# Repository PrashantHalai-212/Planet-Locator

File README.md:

# Planet Locator – GPS Planet Finder

Battery-powered board that shows which planets are in your sky right now. It gets time and position from GPS, calculates where the Moon and planets are directly on an ESP32-C3, and lights an LED for every planet higher than 25° above the horizon. Designed in KiCad 10, 2-layer round PCB made by AISLER, hand-assembled. Group project with Bineth for Practical Electronics (WS 2026) at Rhine-Waal University.

## Specs

| | |
|---|---|
| **MCU** | ESP32-C3-WROOM-02-N4 (RISC-V 160 MHz, 4 MB flash, native USB) |
| **GPS** | u-blox SAM-M10Q, built-in patch antenna, UART at 9600 baud |
| **Output** | 9 × WS2812B RGB LEDs (one per body) + SSD1306 OLED over I²C |
| **Battery** | 1-cell Li-Po, JST PH, built-in protection |
| **Charging** | Microchip MCP73831, 500 mA, 4.2 V |
| **3.3 V supply** | TI TPS63001 buck-boost (works from 1.8 V to 5.5 V input) |
| **Power path** | SS14 Schottky (USB) + DMG2301L P-MOSFET (battery), load sharing |
| **GPS backup** | MCP1700 LDO from the battery, always on |
| **USB** | USB-C (5.1 kΩ CC pull-downs), USBLC6-2 ESD protection, 22 Ω series |
| **Inputs** | EN and BOOT buttons (BOOT doubles as user button), slide switch |
| **PCB** | 2 layers, Ø 90 mm round, 1.6 mm, 0603 parts, AISLER design rules |

## How it works

The planet positions are calculated live on the chip with Paul Schlyter's method, with no lookup tables:

1. GPS gives UTC time, latitude and longitude
2. Day number since 1 Jan 2000
3. Six orbital elements per planet, then Kepler's equation gives the position around the Sun
4. Move the centre from the Sun to the Earth (plus three corrections for the Moon)
5. Tilt by Earth's axis to get right ascension and declination
6. Local sidereal time turns that into altitude and compass direction
7. LED on if the planet is more than **25°** above the horizon

Checked against the PyEphem library: within **0.3°**, and the 25° on/off decision matched in **2700 of 2700** test cases.

## Design decisions

**Stable 3.3 V (TPS63001):** a buck-boost converter keeps exactly 3.3 V from a full battery (4.2 V) down to an empty one. The ESP32 never browns out, and the LEDs keep the same colour and brightness all the way down.

**Charge and play:** when USB is plugged in, it powers the board through an SS14 Schottky diode while the MCP73831 charges the battery. A DMG2301L P-MOSFET switches the board back to the battery the moment USB is unplugged.
- `PROG = 2 kΩ` → 1000 / 2000 = **500 mA** charge current
- The `STAT` output drives a green charging LED

**Works indoors:** the last GPS position is saved in flash. A separate MCP1700 LDO keeps the GPS backup domain alive from the battery even when the switch is off, so time and satellite data are ready immediately.

**Battery level:** a 100k/100k divider on the *switched* battery line feeds the ADC, so it draws nothing when the board is off.

**Reset:** 10 kΩ + 1 µF on EN, as Espressif recommends.

**PCB:**
- 2 layers, round, 90 mm across
- The ESP32 antenna sits over an 18 mm cut-out with no copper underneath
- Ground pour on both sides, tied together with 130 vias
- 0.4 mm power tracks
- USB routed as length-matched differential pairs
- 14 test points on every power rail, GPS, UART0 and the charger status
- 2 × M3 mounting holes

## Pin map

| Function | GPIO |
|---|---|
| GPS UART RX / TX | IO5 / IO6 |
| LED data (WS2812B chain, 330 Ω) | IO4 |
| OLED SDA / SCL | IO0 / IO1 |
| Battery voltage (ADC) | IO3 |
| BOOT / user button | IO9 |
| USB D− / D+ | IO18 / IO19 |
| UART0 TX / RX (test pads) | TX0 / RX0 |

**LED chain order:** Mercury → Venus → Mars → Jupiter → Saturn → Uranus → Neptune → Pluto → Moon

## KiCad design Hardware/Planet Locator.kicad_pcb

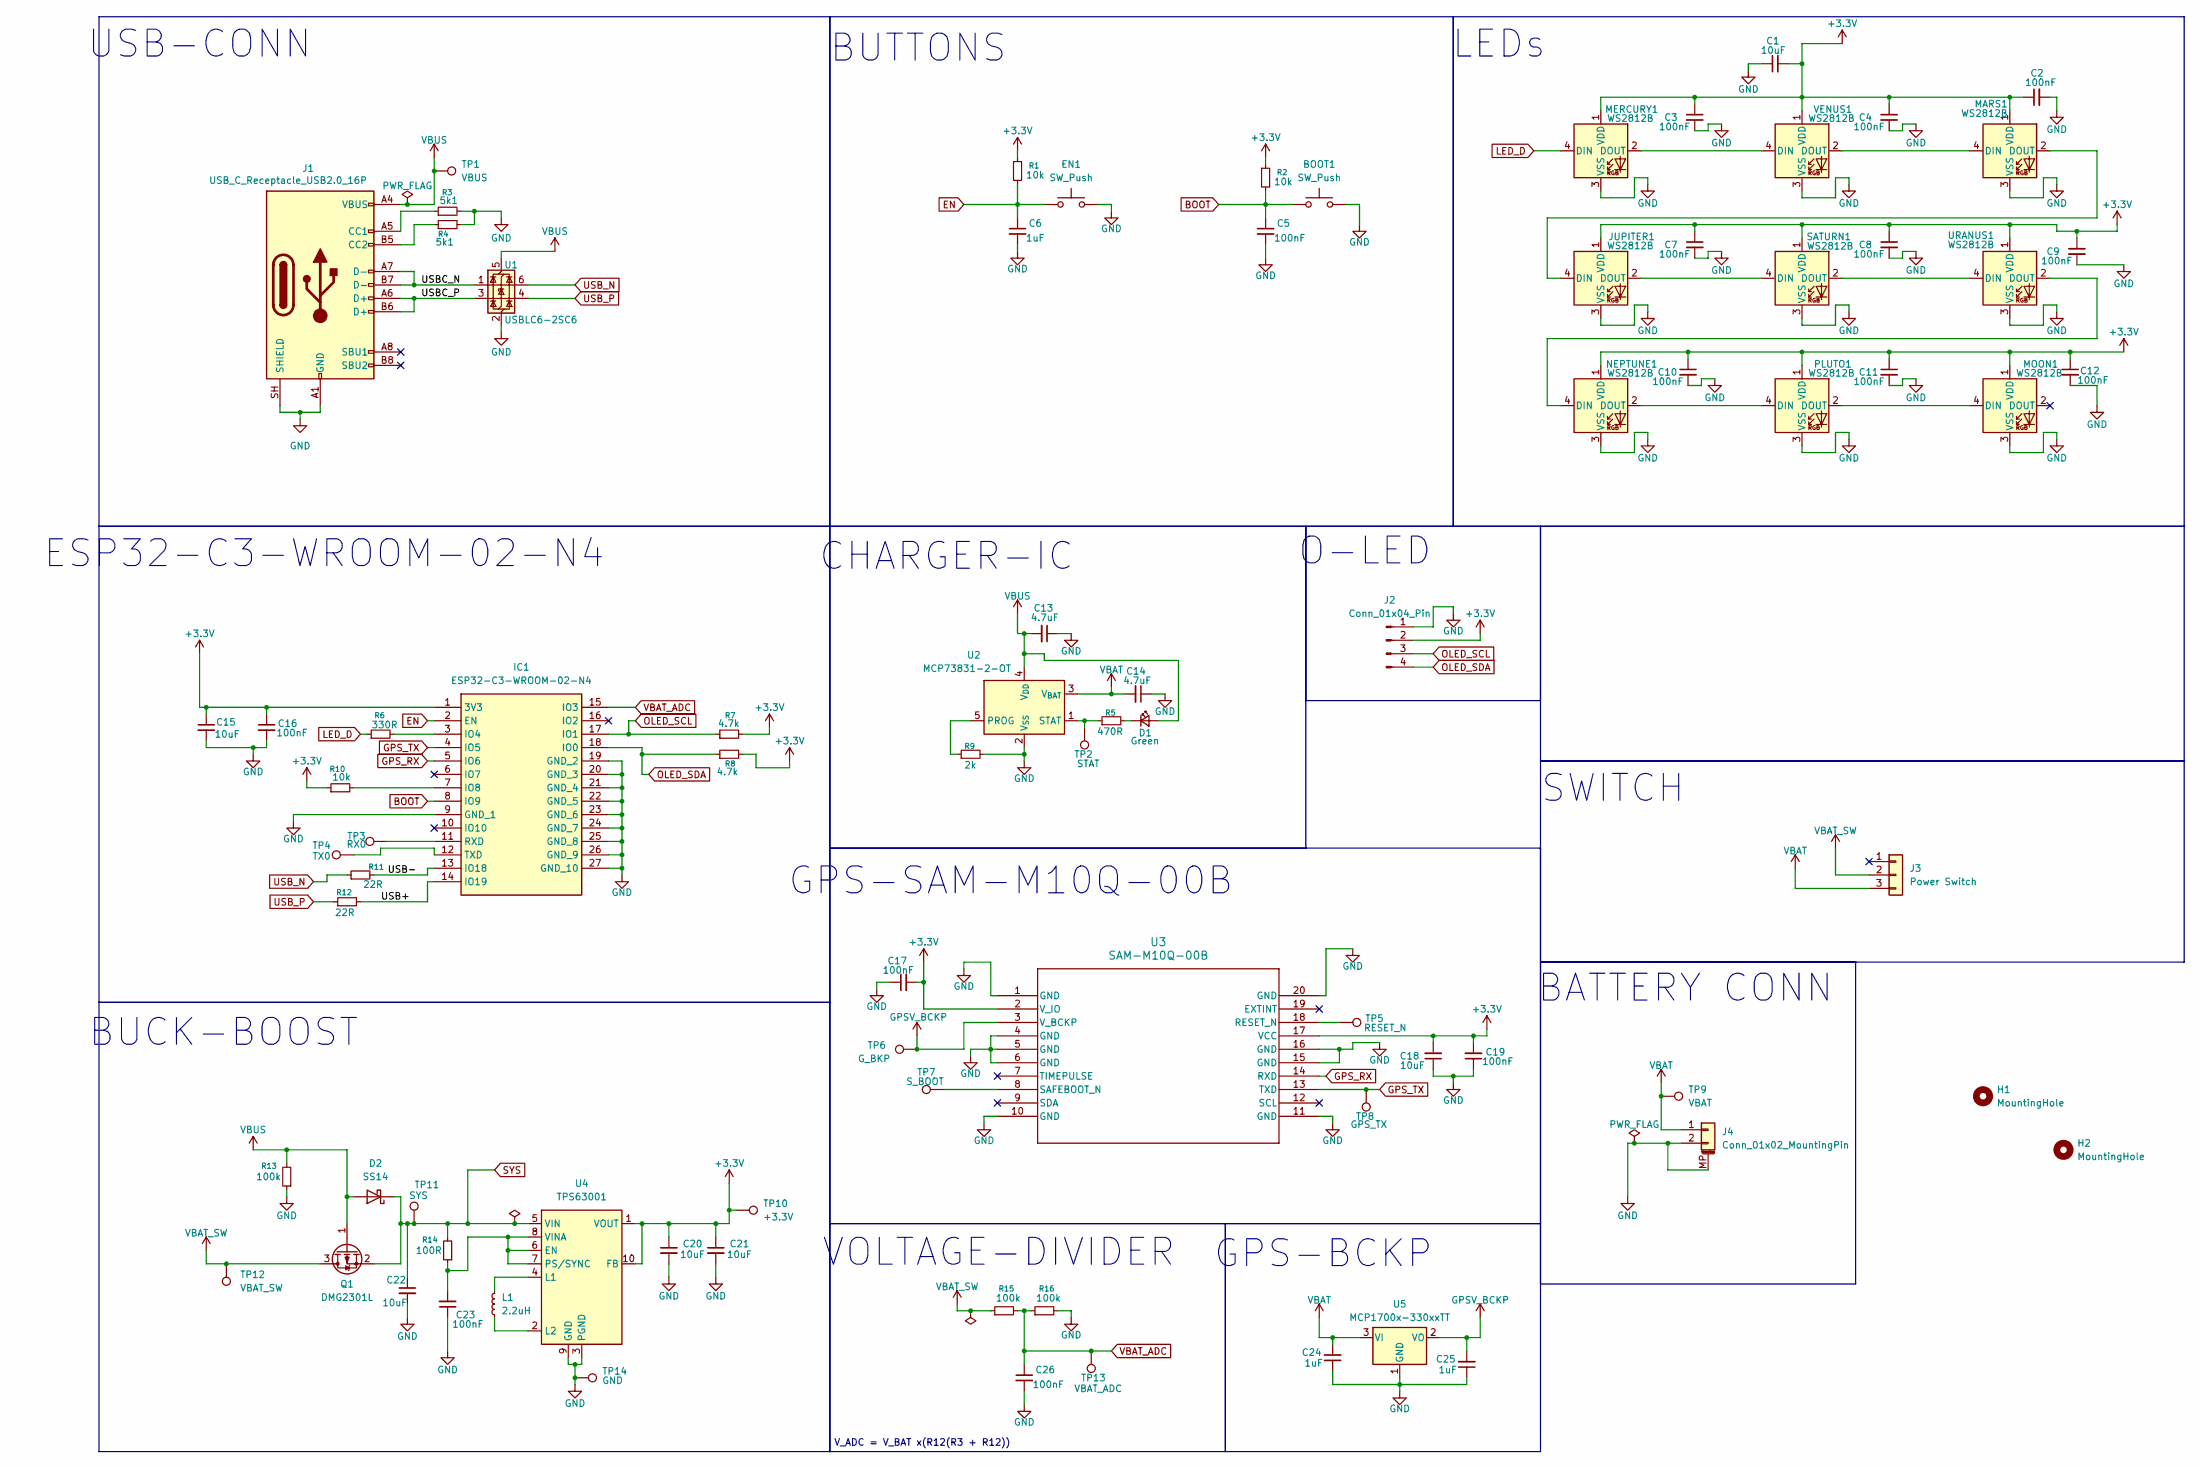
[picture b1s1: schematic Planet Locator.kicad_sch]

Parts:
BOOT1: SW_Push; SW_PUSH_6mm_H7.3mm
C1, C15, C18, C20, C21, C22: 10uF; C_0603_1608Metric_Pad1.08x0.95mm_HandSolder
C2, C3, C4, C5, C7, C8, C9, C10, C11, C12, C16, C17, C19, C23, C26: 100nF; C_0603_1608Metric_Pad1.08x0.95mm_HandSolder
C6, C24, C25: 1uF; C_0603_1608Metric_Pad1.08x0.95mm_HandSolder
C13, C14: 4.7uF; C_0603_1608Metric_Pad1.08x0.95mm_HandSolder
D1: Green; LED_0603_1608Metric
D2: SS14; D_SMA
EN1: SW_Push; SW_PUSH_6mm_H7.3mm
H1, H2: MountingHole; MountingHole_3.2mm_M3
IC1: ESP32-C3-WROOM-02-N4; ESP32C3WROOM02N4; Mouser Part Number 356-ESP32C3WROOM02N4
J1: USB_C_Receptacle_USB2.0_16P; USB_C_Receptacle_GCT_USB4105-xx-A_16P_TopMnt_Horizontal
J2: Conn_01x04_Pin; PinHeader_1x04_P2.54mm_Vertical
J3: Power Switch; PinHeader_1x03_P2.54mm_Vertical
J4: Conn_01x02_MountingPin; JST_PH_S2B-PH-SM4-TB_1x02-1MP_P2.00mm_Horizontal
JUPITER1: WS2812B; LED_WS2812B_PLCC4_5.0x5.0mm_P3.2mm
L1: 2.2uH; L_Bourns-SRN4018
MARS1: WS2812B; LED_WS2812B_PLCC4_5.0x5.0mm_P3.2mm
MERCURY1: WS2812B; LED_WS2812B_PLCC4_5.0x5.0mm_P3.2mm
MOON1: WS2812B; LED_WS2812B_PLCC4_5.0x5.0mm_P3.2mm
NEPTUNE1: WS2812B; LED_WS2812B_PLCC4_5.0x5.0mm_P3.2mm
PLUTO1: WS2812B; LED_WS2812B_PLCC4_5.0x5.0mm_P3.2mm
Q1: DMG2301L; SOT-23
R1, R2, R10: 10k; R_0603_1608Metric_Pad0.98x0.95mm_HandSolder
R3, R4: 5k1; R_0603_1608Metric_Pad0.98x0.95mm_HandSolder
R5: 470R; R_0603_1608Metric_Pad0.98x0.95mm_HandSolder
R6: 330R; R_0603_1608Metric_Pad0.98x0.95mm_HandSolder
R7, R8: 4.7k; R_0603_1608Metric_Pad0.98x0.95mm_HandSolder
R9: 2k; R_0603_1608Metric_Pad0.98x0.95mm_HandSolder
R11, R12: 22R; R_0603_1608Metric_Pad0.98x0.95mm_HandSolder
R13, R15, R16: 100k; R_0603_1608Metric_Pad0.98x0.95mm_HandSolder
R14: 100R; R_0603_1608Metric_Pad0.98x0.95mm_HandSolder
SATURN1: WS2812B; LED_WS2812B_PLCC4_5.0x5.0mm_P3.2mm
TP1: VBUS; TestPoint_Pad_D1.5mm
TP2: STAT; TestPoint_Pad_D1.5mm
TP3: RX0; TestPoint_Pad_D1.5mm
TP4: TX0; TestPoint_Pad_D1.5mm
TP5: RESET_N; TestPoint_Pad_D1.5mm
TP6: G_BKP; TestPoint_Pad_D1.5mm
TP7: S_BOOT; TestPoint_Pad_D1.5mm
TP8: GPS_TX; TestPoint_Pad_D1.5mm
TP9: VBAT; TestPoint_Pad_D1.5mm
TP10: +3.3V; TestPoint_Pad_D1.5mm
TP11: SYS; TestPoint_Pad_D1.5mm
TP12: VBAT_SW; TestPoint_Pad_D1.5mm
TP13: VBAT_ADC; TestPoint_Pad_D1.5mm
TP14: GND; TestPoint_Pad_D1.5mm
U1: USBLC6-2SC6; SOT-23-6
U2: MCP73831-2-OT; SOT-23-5
U3: SAM-M10Q-00B; SAM-M10Q_00B
U4: TPS63001; Texas_DRC0010J_ThermalVias
U5: MCP1700x-330xxTT; SOT-23
URANUS1: WS2812B; LED_WS2812B_PLCC4_5.0x5.0mm_P3.2mm
VENUS1: WS2812B; LED_WS2812B_PLCC4_5.0x5.0mm_P3.2mm

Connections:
+3.3V: C1.2, C2.1, C3.1, C4.1, C7.1, C8.1, C9.1, C10.1, C11.1, C12.1, C15.1, C16.1, C17.2, C18.2, C19.2, C20.1, C21.1, IC1.1 (3V3), J2.2, JUPITER1.1 (VDD), MARS1.1 (VDD), MERCURY1.1 (VDD), MOON1.1 (VDD), NEPTUNE1.1 (VDD), PLUTO1.1 (VDD), R1.1, R2.1, R7.2, R8.2, R10.1, SATURN1.1 (VDD), TP10.1 (1_1), U3.2 (V_IO), U3.17 (VCC), U4.1 (VOUT), U4.10 (FB), URANUS1.1 (VDD), VENUS1.1 (VDD)
/USB+: IC1.14 (IO19), R12.2
/USB-: IC1.13 (IO18), R11.2
/USBC_N: J1.A7 (D-), J1.B7 (D-), U1.1 (I/O1)
/USBC_P: J1.A6 (D+), J1.B6 (D+), U1.3 (I/O2)
BOOT: BOOT1.1, C5.1, IC1.8 (IO9), R2.2
EN: C6.1, EN1.1, IC1.2 (EN), R1.2
GND: BOOT1.2, C1.1, C2.2, C3.2, C4.2, C5.2, C6.2, C7.2, C8.2, C9.2, C10.2, C11.2, C12.2, C13.1, C14.1, C15.2, C16.2, C17.1, C18.1, C19.1, C20.2, C21.2, C22.2, C23.1, C24.1, C25.1, C26.2, EN1.2, IC1.9 (GND_1), IC1.19 (GND_2), IC1.20 (GND_3), IC1.21 (GND_4), IC1.22 (GND_5), IC1.23 (GND_6), IC1.24 (GND_7), IC1.25 (GND_8), IC1.26 (GND_9), IC1.27 (GND_10), J1.A1 (GND), J1.A12 (GND), J1.B1 (GND), J1.B12 (GND), J1.SH (SHIELD), J2.1, J4.2, J4.MP (MountPin), JUPITER1.3 (VSS), MARS1.3 (VSS), MERCURY1.3 (VSS), MOON1.3 (VSS), NEPTUNE1.3 (VSS), PLUTO1.3 (VSS), R3.2, R4.2, R9.2, R13.1, R16.2, SATURN1.3 (VSS), TP14.1 (1_1), U1.2 (GND), U2.2 (V_{SS}), U3.1 (GND), U3.4 (GND), U3.5 (GND), U3.6 (GND), U3.10 (GND), U3.11 (GND), U3.15 (GND), U3.16 (GND), U3.20 (GND), U4.3 (PGND), U4.9 (GND), U4.11 (PGND), U5.1 (GND), URANUS1.3 (VSS), VENUS1.3 (VSS)
GPSV_BCKP: C25.2, TP6.1 (1_1), U3.3 (V_BCKP), U5.2 (VO)
GPS_RX: IC1.5 (IO6), U3.14 (RXD)
GPS_TX: IC1.4 (IO5), TP8.1 (1_1), U3.13 (TXD)
LED_D: MERCURY1.4 (DIN), R6.1
unnamed: D1.1 (K), R5.2
unnamed: IC1.3 (IO4), R6.2
unnamed: IC1.7 (IO8), R10.2
unnamed: IC1.11 (RXD), TP3.1 (1_1)
unnamed: IC1.12 (TXD), TP4.1 (1_1)
unnamed: J1.A5 (CC1), R3.1
unnamed: J1.B5 (CC2), R4.1
unnamed: JUPITER1.4 (DIN), MARS1.2 (DOUT)
unnamed: JUPITER1.2 (DOUT), SATURN1.4 (DIN)
unnamed: MARS1.4 (DIN), VENUS1.2 (DOUT)
unnamed: MERCURY1.2 (DOUT), VENUS1.4 (DIN)
unnamed: MOON1.4 (DIN), PLUTO1.2 (DOUT)
unnamed: NEPTUNE1.4 (DIN), URANUS1.2 (DOUT)
unnamed: NEPTUNE1.2 (DOUT), PLUTO1.4 (DIN)
unnamed: SATURN1.2 (DOUT), URANUS1.4 (DIN)
unnamed: R9.1, U2.5 (PROG)
unnamed: R5.1, TP2.1 (1_1), U2.1 (STAT)
unnamed: TP5.1 (1_1), U3.18 (RESET_N)
unnamed: TP7.1 (1_1), U3.8 (SAFEBOOT_N)
unnamed: C23.2, R14.1, U4.6 (EN), U4.7 (PS/SYNC), U4.8 (VINA)
unnamed: L1.2, U4.4 (L1)
unnamed: L1.1, U4.2 (L2)
OLED_SCL: IC1.17 (IO1), J2.3, R7.1
OLED_SDA: IC1.18 (IO0), J2.4, R8.1
SYS: C22.1, D2.1 (K), Q1.2 (S), R14.2, TP11.1 (1_1), U4.5 (VIN)
USB_N: R11.1, U1.6 (I/O1)
USB_P: R12.1, U1.4 (I/O2)
VBAT: C14.2, C24.2, J3.3, J4.1, TP9.1 (1_1), U2.3 (V_{BAT}), U5.3 (VI)
VBAT_ADC: C26.1, IC1.15 (IO3), R15.2, R16.1, TP13.1 (1_1)
VBAT_SW: J3.2, Q1.3 (D), R15.1, TP12.1 (1_1)
VBUS: C13.2, D1.2 (A), D2.2 (A), J1.A4 (VBUS), J1.A9 (VBUS), J1.B4 (VBUS), J1.B9 (VBUS), Q1.1 (G), R13.2, TP1.1 (1_1), U1.5 (VBUS), U2.4 (V_{DD})

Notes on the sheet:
O-LED
BUCK-BOOST
LEDs
V_ADC = V_BAT x(R12(R3 + R12))
SWITCH
GPS-BCKP
USB-CONN
ESP32-C3-WROOM-02-N4
BATTERY CONN
GPS-SAM-M10Q-00B
VOLTAGE-DIVIDER
CHARGER-IC
BUTTONS

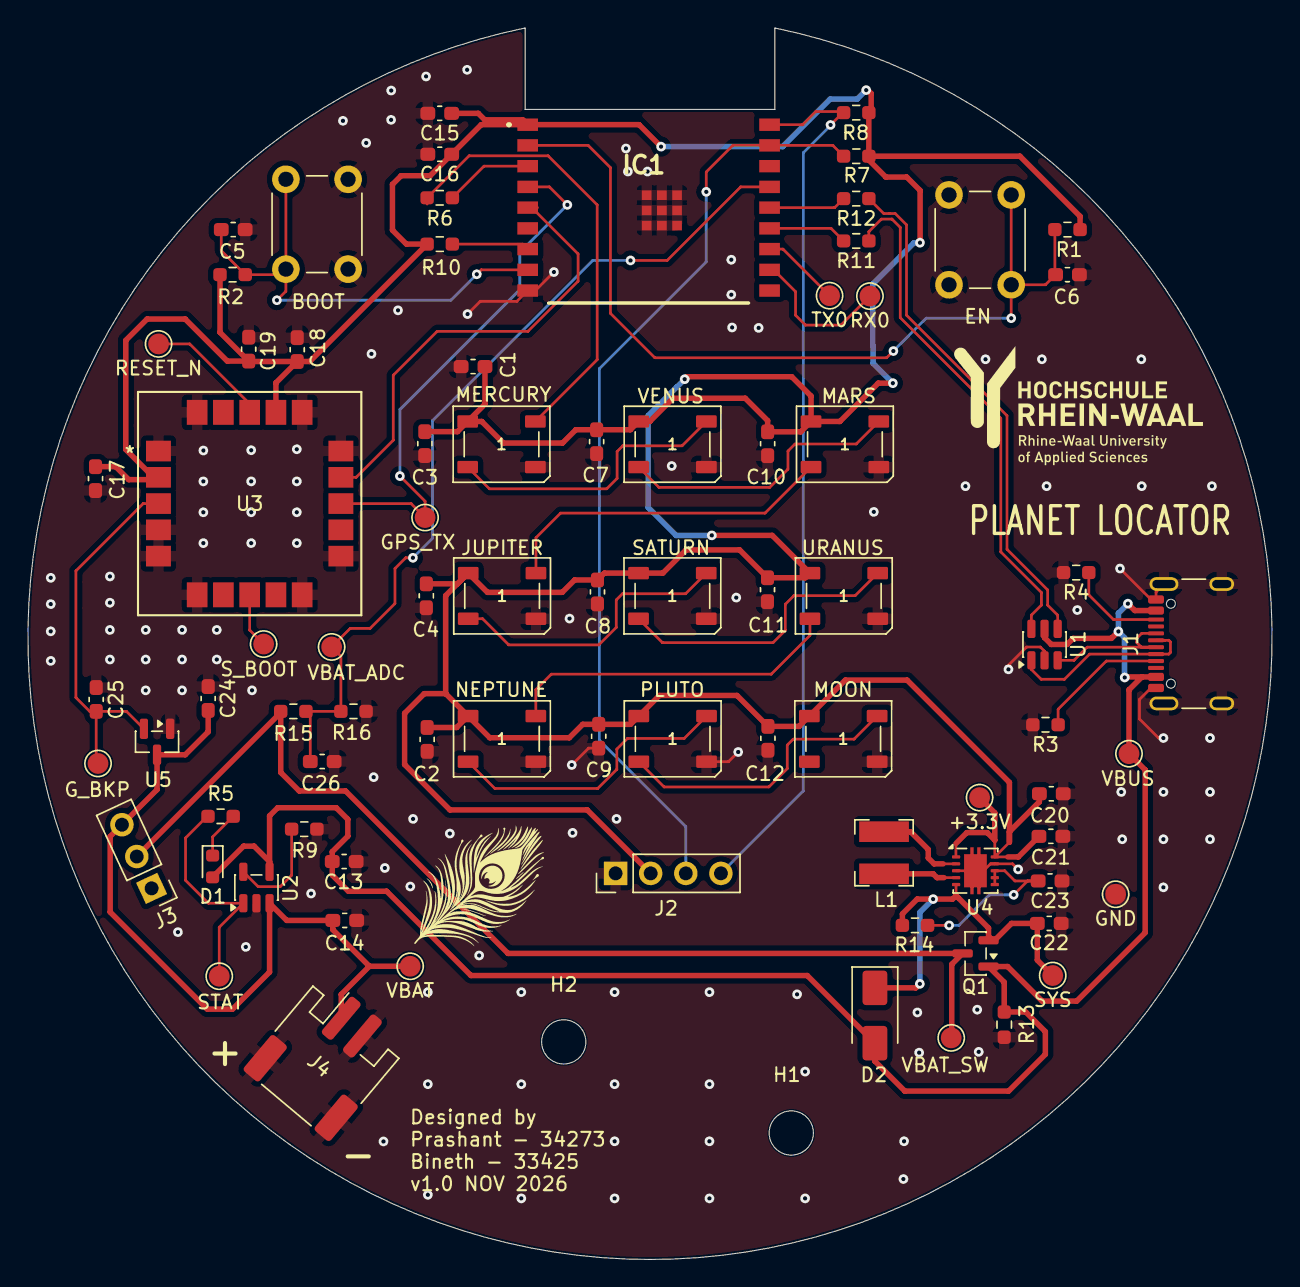
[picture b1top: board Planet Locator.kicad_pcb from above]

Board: 2 copper layers, 90.0 x 89.1 mm, 83 parts (0 on the bottom side), 43 nets.
